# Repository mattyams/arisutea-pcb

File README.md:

# Arisutea - Arisu Keyboard PCB with More Modifications...now with MORE!

### Arisutea Keyboard Variants
- [STM32](https://github.com/mattyams/arisutea-pcb-stm32) - Prototypes Received. STM32F072 MCU, board is being tested.
- [SK6812MiniE](https://github.com/mattyams/arisutea-pcb-rgb) - In Progress. PCB designed, just need to do some QC.
- [Bluetooth](https://github.com/mattyams/arisutea-pcb-bt) - In Progress. Initial design for the PCB is ongoing, need to research more on the MCU and batteries.

## Disclaimer: Use these files at your own risk.
アリステア PCB designed using KiCad. The layout was originally created by FateNozomi, inspired by Lyn's EM7 and TGR Alice with some modification. The layout was then modified by CorruptedJef and robotictomato to add USB-C, ESD and to shift/add some keys. This inspired me to modify the layout further by adding the ability to swap your switches out whenever you want and to make some keys a little more permenant. I have designed many boards in the past but never a keyboard so this is my first crack at it and I figured why not go all out? If you notice any issue please open an issue and we can discuss!

Since the layout has been modified yet again I decided to give the project a new name, Arisutea, which translates to Alistair. Obviously keeping the theme running here. 

Check out the iBOM [here](https://htmlpreview.github.io/?https://raw.githubusercontent.com/mattyams/arisutea-pcb/master/hardware/BOM/arisutea-rev1.0-ibom.html)! This was generated with [InteractiveHtmlBom](https://github.com/openscopeproject/InteractiveHtmlBom)!

Key modifications to the PCB:
- Added in Kailh Hotswap sockets.
- Addition of full backspace position, connected to switch 59 (row 0, column 13).
  - Removed switch 63 and repositioned switch 59 to add full backspace position.
- USB-C ESD rework.
- Added underglow LED strip support (v0.6+)
- Added LED indicators for CAPS and NUM lock as well as layer. (v0.6+)
- Updated JSON layout file for this particular keyboard.
- Original mounting holes have been returned to their rightful place. The idea of widening them was good at the time for FR4 plates, but not very practical. I am redesigning the case to allow for brass inserts and standoffs to be installed so the PCB will be nice and snug. More on that later. FR4 plates still will work but you will have to drill the holes out manually. If you take this route....go forth cautiously adventurer.

Renders generated by [Tracespace](https://github.com/tracespace/tracespace).

v0.6+

Just some recent builds...

Messing around with different switches.

# QMK Firmware
This can be located in the [firmware](https://github.com/mattyams/arisutea-pcb/tree/master/firmware) folder. 

# Case Files for Ponoko

Case files are updated to reflect changes to the full backspace on switch 59 and can be found in the hardware folder under [arisutea-case](https://github.com/mattyams/arisutea-pcb/tree/master/hardware/arisutea-case).  The case I ordered with these changes just came in this week (3/6/2021) and it works very well with the changes I made to the full backspace and addition of the stablizer on the prototypes designed by CorruptedJef and robotictomato. There is now a "boxed" version of the case that I have made that is designed to work with some wrist rests that do not have the ortho shape AND case files for version 0.6+ PCBs that include the indicator LEDs, I have not ordered/tested these but will soon.

# FR4 Plates and Case

Additionaly I have created files for FR4 plates to be made and used with this layout. These can be found in the hardware folder under [FR4_Plates](https://github.com/mattyams/arisutea-pcb/tree/master/hardware/FR4_Plates). The plates are designed to fit with the full backspace and non-stepped capslock. That being said, these will not work on the original Fate Designs PCB. No plans to create plates for the LED indicators on the v0.6+ PCBs. NOTE FOR v0.6.3+ PCBs! FR4 plates still will work but you will have to drill the holes out manually. If you take this route....go forth cautiously adventurer.

## Exceprts from original designer, FateNozomi:

Key differences:
- Removed the extra [B] key on the right half and shifted the [NM,.?] row to the left by 0.25U.
- Shifted the 3 keys to the right and added arrow keys.
- Tweaked the bottom so that the 1.5U keys doesn't protrude out a little.

Shifting the [NM,.?] row to the left by 0.25U required quite some work on the arrangement of keys for the right half.
As a result, this does not give the same typing experience as Lyn's EM7 and TGR Alice.
Lyn's EM7 and TGR Alice uses the home row as the center point to vertically align both halves while I used the number row instead.
Due to the nature of staggered keyboards, aligning using the number row resulted in the home row not being aligned.

Disclaimer: Use these files at your own risk.

## Gerber Files
Download the gerber files under [releases](https://github.com/mattyams/arisutea-pcb/releases).

## PCB Assembly
For the components required, you may refer to the bill of materials included along with the release as reference or load up the design file in KiCad.
All the components can be soldered using a regular soldering iron, though soldering the USB-C receptacle might be the biggest hurdle. I have made an adjustment to the USB footprint to allow for a little more error when handsoldering. POS files have been removed due to the overwhelming amount of compatibility issues of placement and selection. The BOM will remain for part numbers from LCSC and board placement.

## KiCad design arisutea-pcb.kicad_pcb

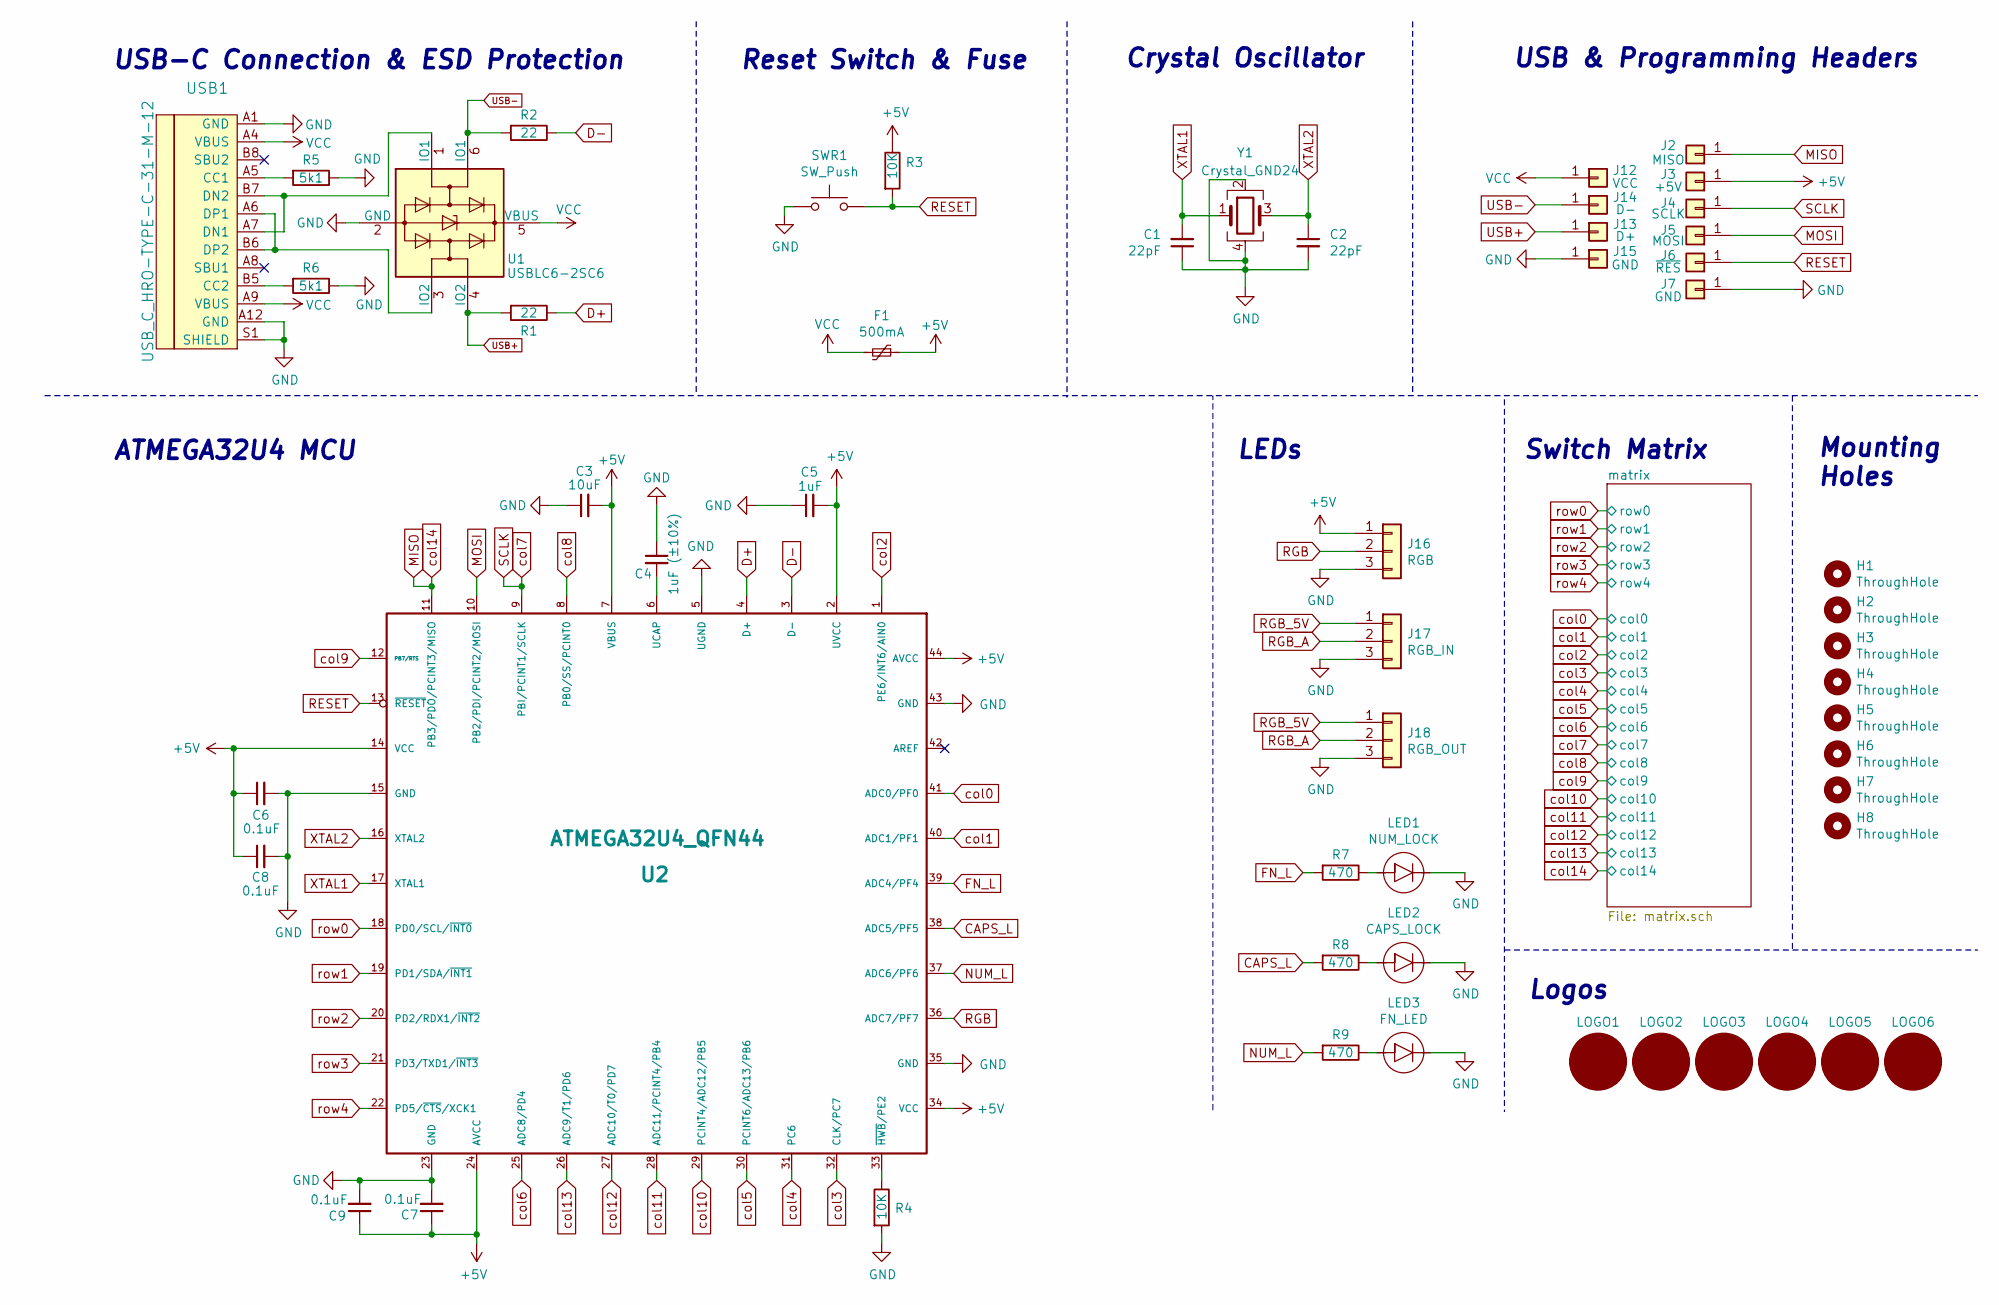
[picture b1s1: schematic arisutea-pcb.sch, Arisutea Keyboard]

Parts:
C1, C2: 22pF; C_0805_2012Metric_Pad1.18x1.45mm_HandSolder; LCSC C1804
C3: 10uF; C_0805_2012Metric_Pad1.18x1.45mm_HandSolder; LCSC C15850
C4: 1uF (±10%); C_0805_2012Metric_Pad1.18x1.45mm_HandSolder; LCSC C28323
C5: 1uF; C_0805_2012Metric_Pad1.18x1.45mm_HandSolder; LCSC C28323
C6, C7, C8, C9: 0.1uF; C_0805_2012Metric_Pad1.18x1.45mm_HandSolder; LCSC C28233
F1: 500mA; Fuse_1206_3216Metric_Pad1.42x1.75mm_HandSolder; LCSC C70068
H1, H2, H3, H4, H5, H6, H7, H8: ThroughHole; Generic-Mounthole
J2: MISO; PinHeader_1x01_P2.54mm_Vertical
J3: +5V; PinHeader_1x01_P2.54mm_Vertical
J4: SCLK; PinHeader_1x01_P2.54mm_Vertical
J5: MOSI; PinHeader_1x01_P2.54mm_Vertical
J6: ~RES~; PinHeader_1x01_P2.54mm_Vertical
J7, J15: GND; PinHeader_1x01_P2.54mm_Vertical
J12: VCC; PinHeader_1x01_P2.54mm_Vertical
J13: D+; PinHeader_1x01_P2.54mm_Vertical
J14: D-; PinHeader_1x01_P2.54mm_Vertical
J16: RGB; PinHeader_1x03_P2.54mm_Vertical
J17: RGB_IN; PinHeader_1x03_P2.54mm_Vertical
J18: RGB_OUT; PinHeader_1x03_P2.54mm_Vertical
LED1: NUM_LOCK; LED_IN-S124ARUW; LCSC C401114
LED2: CAPS_LOCK; LED_IN-S124ARUW; LCSC C401114
LED3: FN_LED; LED_IN-S124ARUW; LCSC C401114
LOGO1, LOGO2: arisutea_logo
LOGO3, LOGO4: QMK Logo; OSHW-Logo_11.4x12mm_SilkScreen
LOGO5, LOGO6: QMK_Logo_Light
R1, R2: 22; R_0805_2012Metric_Pad1.20x1.40mm_HandSolder; LCSC C17561
R3, R4: 10K; R_0805_2012Metric_Pad1.20x1.40mm_HandSolder; LCSC C17414
R5, R6: 5k1; R_0805_2012Metric_Pad1.20x1.40mm_HandSolder; LCSC C27834
R7, R8, R9: 470; R_0805_2012Metric_Pad1.20x1.40mm_HandSolder; LCSC C27834
SWR1: SW_Push; SW_SPST_TL3342; LCSC C318884
U1: USBLC6-2SC6; SOT-23-6_Handsoldering; LCSC C7519
U2: ATMEGA32U4_QFN44; TQFP-44_10x10mm_P0.8mm; LCSC C44854
USB1: USB_C_HRO-TYPE-C-31-M-12; USB_C_Receptacle_HRO_TYPE-C-31-M-12-HandSoldering; LCSC C319148
Y1: Crystal_GND24; Crystal_SMD_TXC_7M-4Pin_3.2x2.5mm_HandSoldering; LCSC C89371

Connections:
+5V: C3.2, C5.2, C6.1, C7.1, C8.1, C9.1, F1.1, J3.1, J16.1, R3.1, U2.2 (UVCC), U2.7 (VBUS), U2.14 (VCC), U2.24 (AVCC), U2.34 (VCC), U2.44 (AVCC)
CAPS_L: R8.2, U2.38 (ADC5/PF5)
D+: R1.1, U2.4 (D+)
D-: R2.1, U2.3 (D-)
FN_L: R7.2, U2.39 (ADC4/PF4)
GND: C1.1, C2.2, C3.1, C4.1, C5.1, C6.2, C7.2, C8.2, C9.2, J7.1, J15.1, J16.3, J17.3, J18.3, LED1.C, LED2.C, LED3.C, R4.2, R5.1, R6.1, SWR1.1, U1.2 (GND), U2.5 (UGND), U2.15 (GND), U2.23 (GND), U2.35 (GND), U2.43 (GND), USB1.A1 (GND), USB1.A12 (GND), USB1.S1 (SHIELD), Y1.2, Y1.4
MISO: J2.1, U2.11 (PB3/PDO/PCINT3/MISO); also elsewhere on the board
MOSI: J5.1, U2.10 (PB2/PDI/PCINT2/MOSI)
NUM_L: R9.2, U2.37 (ADC6/PF6)
unnamed: C4.2, U2.6 (UCAP)
unnamed: LED1.A, R7.1
unnamed: LED2.A, R8.1
unnamed: LED3.A, R9.1
unnamed: R4.1, U2.33 (~HWB~/PE2)
unnamed: R5.2, USB1.A5 (CC1)
unnamed: R6.2, USB1.B5 (CC2)
unnamed: U1.1 (IO1), USB1.A7 (DN1), USB1.B7 (DN2)
unnamed: U1.3 (IO2), USB1.A6 (DP1), USB1.B6 (DP2)
RESET: J6.1, R3.2, SWR1.2, U2.13 (~RESET~)
RGB: J16.2, U2.36 (ADC7/PF7)
RGB_5V: J17.1, J18.1
RGB_A: J17.2, J18.2
SCLK: J4.1, U2.9 (PBI/PCINT1/SCLK); also elsewhere on the board
USB+: J13.1, R1.2, U1.4 (IO2)
USB-: J14.1, R2.2, U1.6 (IO1)
VCC: F1.2, J12.1, U1.5 (VBUS), USB1.A4 (VBUS), USB1.A9 (VBUS)
XTAL1: C1.2, U2.17 (XTAL1), Y1.1
XTAL2: C2.1, U2.16 (XTAL2), Y1.3
col0: U2.41 (ADC0/PF0); also elsewhere on the board
col1: U2.40 (ADC1/PF1); also elsewhere on the board
col2: U2.1 (PE6/INT6/AIN0); also elsewhere on the board
col3: U2.32 (CLK/PC7); also elsewhere on the board
col4: U2.31 (PC6); also elsewhere on the board
col5: U2.30 (PCINT6/ADC13/PB6); also elsewhere on the board
col6: U2.25 (ADC8/PD4); also elsewhere on the board
col8: U2.8 (PB0/SS/PCINT0); also elsewhere on the board
col9: U2.12 (PB7/RTS); also elsewhere on the board
col10: U2.29 (PCINT4/ADC12/PB5); also elsewhere on the board
col11: U2.28 (ADC11/PCINT4/PB4); also elsewhere on the board
col12: U2.27 (ADC10/T0/PD7); also elsewhere on the board
col13: U2.26 (ADC9/T1/PD6); also elsewhere on the board
row0: U2.18 (PD0/SCL/~INT0~); also elsewhere on the board
row1: U2.19 (PD1/SDA/~INT1~); also elsewhere on the board
row2: U2.20 (PD2/RDX1/~INT2~); also elsewhere on the board
row3: U2.21 (PD3/TXD1/~INT3~); also elsewhere on the board
row4: U2.22 (PD5/~CTS~/XCK1); also elsewhere on the board

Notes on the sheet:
ATMEGA32U4 MCU
USB-C Connection & ESD Protection
Reset Switch & Fuse
Crystal Oscillator
USB & Programming Headers
LEDs
Switch Matrix
Logos
Mounting Holes

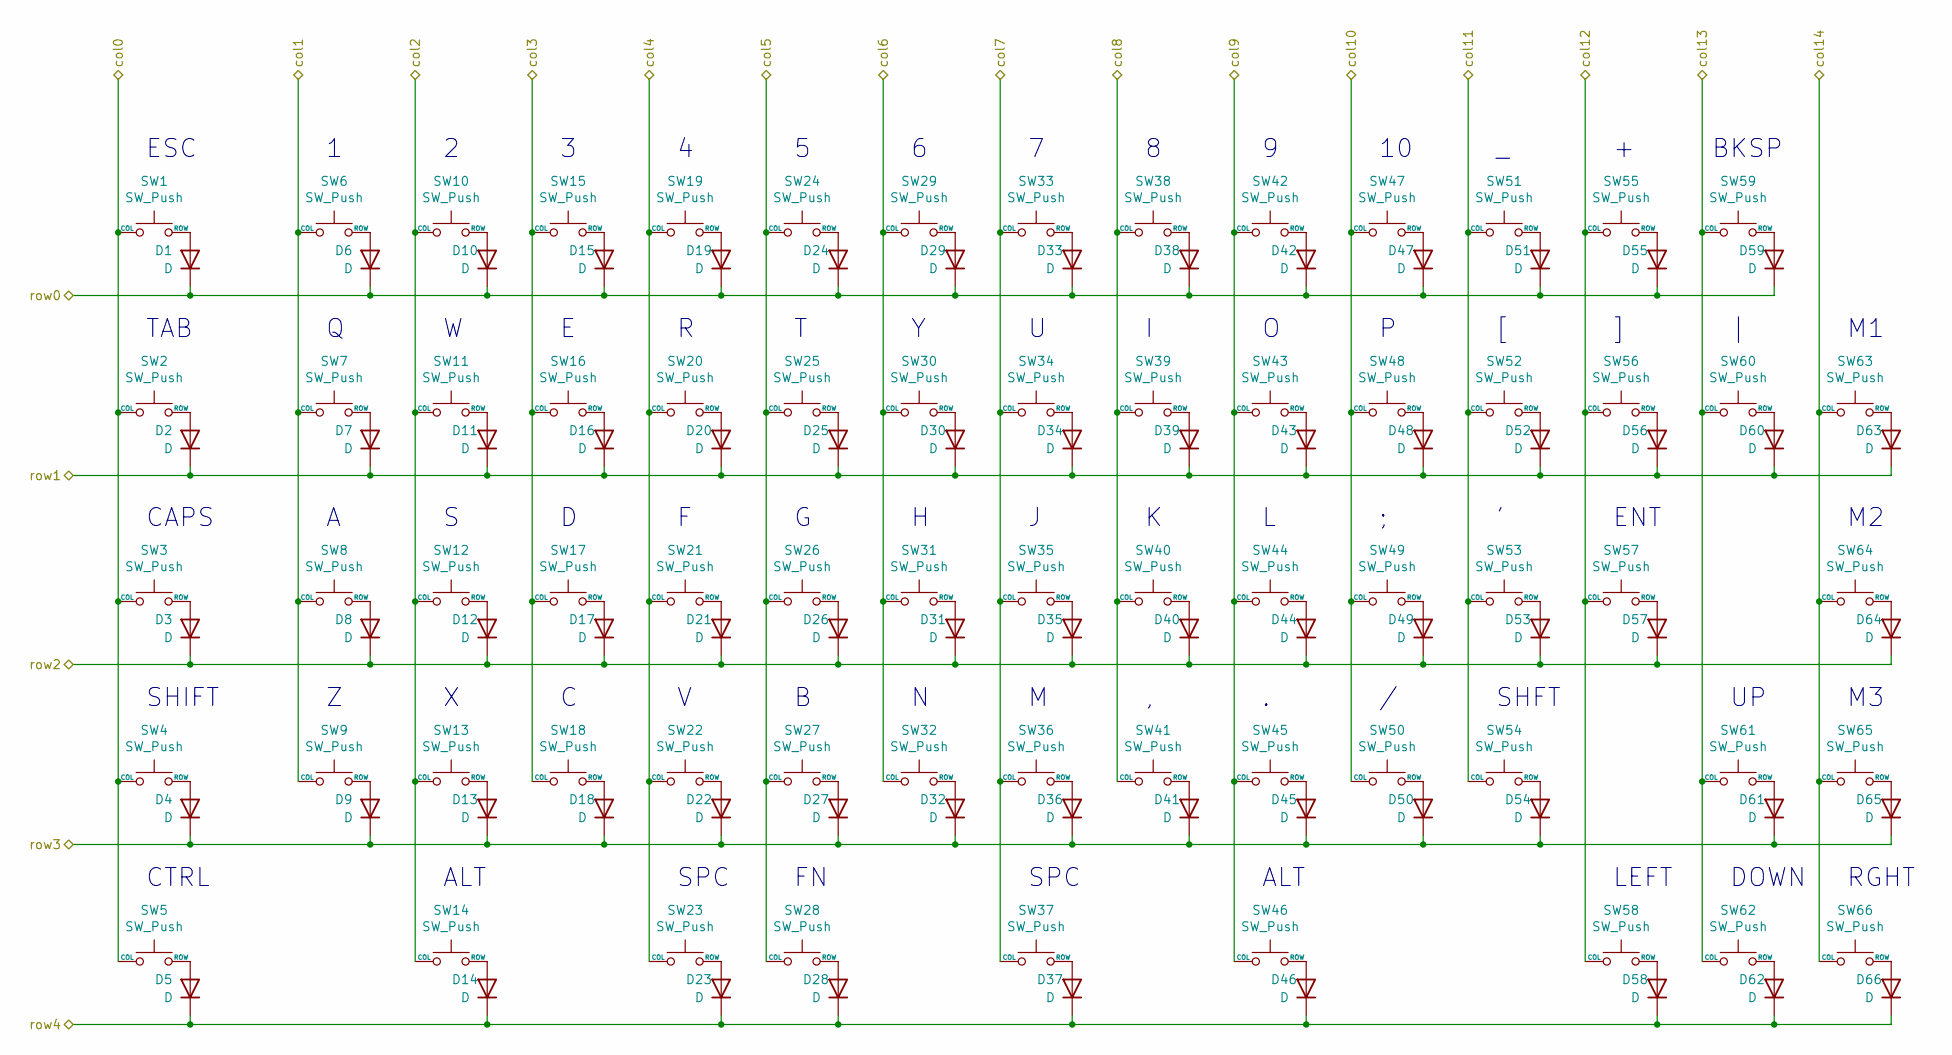
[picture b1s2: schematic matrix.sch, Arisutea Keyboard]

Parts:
D1, D2, D3, D4, D5, D6, D7, D8, D9, D10, D11, D12, D13, D14, D15, D16, D17, D18, D19, D20, D21, D22, D23, D24, D25, D26, D27, D28, D29, D30, D31, D32, D33, D34, D35, D36, D37, D38, D39, D40, D41, D42, D43, D44, D45, D46, D47, D48, D49, D50, D51, D52, D53, D54, D55, D56, D57, D58, D59, D60, D61, D62, D63, D64, D65, D66: D; D_SOD-123; LCSC C81598
SW1, SW6, SW7, SW8, SW9, SW10, SW11, SW12, SW13, SW14, SW15, SW16, SW17, SW18, SW19, SW20, SW21, SW22, SW24, SW25, SW26, SW27, SW28, SW29, SW30, SW31, SW32, SW33, SW34, SW35, SW36, SW38, SW39, SW40, SW41, SW42, SW43, SW44, SW45, SW46, SW47, SW48, SW49, SW50, SW51, SW52, SW53, SW55, SW56, SW58, SW61, SW62, SW63, SW64, SW65, SW66: SW_Push; SW_Hotswap_Kailh_1.00u
SW2, SW5, SW60: SW_Push; SW_Hotswap_Kailh_1.50u
SW3, SW54: SW_Push; SW_Hotswap_Kailh_1.75u
SW4: SW_Push; SW_Hotswap_Kailh_2.25u
SW23: SW_Push; SW_Hotswap_Kailh_2.00u_RevStab
SW37: SW_Push; SW_Hotswap_Kailh_2.75u_RevStab
SW57: SW_Push; SW_Hotswap_Kailh_2.25u_RevStab
SW59: SW_Push; SW_Hotswap_Kailh_2.00u

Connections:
MISO: SW63.1 (COL), SW64.1 (COL), SW65.1 (COL), SW66.1 (COL); also elsewhere on the board
unnamed: D1.2 (A), SW1.2 (ROW)
unnamed: D2.2 (A), SW2.2 (ROW)
unnamed: D3.2 (A), SW3.2 (ROW)
unnamed: D4.2 (A), SW4.2 (ROW)
unnamed: D5.2 (A), SW5.2 (ROW)
unnamed: D6.2 (A), SW6.2 (ROW)
unnamed: D7.2 (A), SW7.2 (ROW)
unnamed: D8.2 (A), SW8.2 (ROW)
unnamed: D9.2 (A), SW9.2 (ROW)
unnamed: D10.2 (A), SW10.2 (ROW)
unnamed: D11.2 (A), SW11.2 (ROW)
unnamed: D12.2 (A), SW12.2 (ROW)
unnamed: D13.2 (A), SW13.2 (ROW)
unnamed: D14.2 (A), SW14.2 (ROW)
unnamed: D15.2 (A), SW15.2 (ROW)
unnamed: D16.2 (A), SW16.2 (ROW)
unnamed: D17.2 (A), SW17.2 (ROW)
unnamed: D18.2 (A), SW18.2 (ROW)
unnamed: D19.2 (A), SW19.2 (ROW)
unnamed: D20.2 (A), SW20.2 (ROW)
unnamed: D21.2 (A), SW21.2 (ROW)
unnamed: D22.2 (A), SW22.2 (ROW)
unnamed: D23.2 (A), SW23.2 (ROW)
unnamed: D24.2 (A), SW24.2 (ROW)
unnamed: D25.2 (A), SW25.2 (ROW)
unnamed: D26.2 (A), SW26.2 (ROW)
unnamed: D27.2 (A), SW27.2 (ROW)
unnamed: D28.2 (A), SW28.2 (ROW)
unnamed: D29.2 (A), SW29.2 (ROW)
unnamed: D30.2 (A), SW30.2 (ROW)
unnamed: D31.2 (A), SW31.2 (ROW)
unnamed: D32.2 (A), SW32.2 (ROW)
unnamed: D33.2 (A), SW33.2 (ROW)
unnamed: D34.2 (A), SW34.2 (ROW)
unnamed: D35.2 (A), SW35.2 (ROW)
unnamed: D36.2 (A), SW36.2 (ROW)
unnamed: D37.2 (A), SW37.2 (ROW)
unnamed: D38.2 (A), SW38.2 (ROW)
unnamed: D39.2 (A), SW39.2 (ROW)
unnamed: D40.2 (A), SW40.2 (ROW)
unnamed: D41.2 (A), SW41.2 (ROW)
unnamed: D42.2 (A), SW42.2 (ROW)
unnamed: D43.2 (A), SW43.2 (ROW)
unnamed: D44.2 (A), SW44.2 (ROW)
unnamed: D45.2 (A), SW45.2 (ROW)
unnamed: D46.2 (A), SW46.2 (ROW)
unnamed: D47.2 (A), SW47.2 (ROW)
unnamed: D48.2 (A), SW48.2 (ROW)
unnamed: D49.2 (A), SW49.2 (ROW)
unnamed: D50.2 (A), SW50.2 (ROW)
unnamed: D51.2 (A), SW51.2 (ROW)
unnamed: D52.2 (A), SW52.2 (ROW)
unnamed: D53.2 (A), SW53.2 (ROW)
unnamed: D54.2 (A), SW54.2 (ROW)
unnamed: D55.2 (A), SW55.2 (ROW)
unnamed: D56.2 (A), SW56.2 (ROW)
unnamed: D57.2 (A), SW57.2 (ROW)
unnamed: D58.2 (A), SW58.2 (ROW)
unnamed: D59.2 (A), SW59.2 (ROW)
unnamed: D60.2 (A), SW60.2 (ROW)
unnamed: D61.2 (A), SW61.2 (ROW)
unnamed: D62.2 (A), SW62.2 (ROW)
unnamed: D63.2 (A), SW63.2 (ROW)
unnamed: D64.2 (A), SW64.2 (ROW)
unnamed: D65.2 (A), SW65.2 (ROW)
unnamed: D66.2 (A), SW66.2 (ROW)
SCLK: SW33.1 (COL), SW34.1 (COL), SW35.1 (COL), SW36.1 (COL), SW37.1 (COL); also elsewhere on the board
col0: SW1.1 (COL), SW2.1 (COL), SW3.1 (COL), SW4.1 (COL), SW5.1 (COL); also elsewhere on the board
col1: SW6.1 (COL), SW7.1 (COL), SW8.1 (COL), SW9.1 (COL); also elsewhere on the board
col2: SW10.1 (COL), SW11.1 (COL), SW12.1 (COL), SW13.1 (COL), SW14.1 (COL); also elsewhere on the board
col3: SW15.1 (COL), SW16.1 (COL), SW17.1 (COL), SW18.1 (COL); also elsewhere on the board
col4: SW19.1 (COL), SW20.1 (COL), SW21.1 (COL), SW22.1 (COL), SW23.1 (COL); also elsewhere on the board
col5: SW24.1 (COL), SW25.1 (COL), SW26.1 (COL), SW27.1 (COL), SW28.1 (COL); also elsewhere on the board
col6: SW29.1 (COL), SW30.1 (COL), SW31.1 (COL), SW32.1 (COL); also elsewhere on the board
col8: SW38.1 (COL), SW39.1 (COL), SW40.1 (COL), SW41.1 (COL); also elsewhere on the board
col9: SW42.1 (COL), SW43.1 (COL), SW44.1 (COL), SW45.1 (COL), SW46.1 (COL); also elsewhere on the board
col10: SW47.1 (COL), SW48.1 (COL), SW49.1 (COL), SW50.1 (COL); also elsewhere on the board
col11: SW51.1 (COL), SW52.1 (COL), SW53.1 (COL), SW54.1 (COL); also elsewhere on the board
col12: SW55.1 (COL), SW56.1 (COL), SW57.1 (COL), SW58.1 (COL); also elsewhere on the board
col13: SW59.1 (COL), SW60.1 (COL), SW61.1 (COL), SW62.1 (COL); also elsewhere on the board
row0: D1.1 (K), D6.1 (K), D10.1 (K), D15.1 (K), D19.1 (K), D24.1 (K), D29.1 (K), D33.1 (K), D38.1 (K), D42.1 (K), D47.1 (K), D51.1 (K), D55.1 (K), D59.1 (K); also elsewhere on the board
row1: D2.1 (K), D7.1 (K), D11.1 (K), D16.1 (K), D20.1 (K), D25.1 (K), D30.1 (K), D34.1 (K), D39.1 (K), D43.1 (K), D48.1 (K), D52.1 (K), D56.1 (K), D60.1 (K), D63.1 (K); also elsewhere on the board
row2: D3.1 (K), D8.1 (K), D12.1 (K), D17.1 (K), D21.1 (K), D26.1 (K), D31.1 (K), D35.1 (K), D40.1 (K), D44.1 (K), D49.1 (K), D53.1 (K), D57.1 (K), D64.1 (K); also elsewhere on the board
row3: D4.1 (K), D9.1 (K), D13.1 (K), D18.1 (K), D22.1 (K), D27.1 (K), D32.1 (K), D36.1 (K), D41.1 (K), D45.1 (K), D50.1 (K), D54.1 (K), D61.1 (K), D65.1 (K); also elsewhere on the board
row4: D5.1 (K), D14.1 (K), D23.1 (K), D28.1 (K), D37.1 (K), D46.1 (K), D58.1 (K), D62.1 (K), D66.1 (K); also elsewhere on the board

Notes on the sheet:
ESC
TAB
ENT
RGHT
LEFT
DOWN
SPC
ALT
CTRL
SHFT
SHIFT
CAPS
BKSP

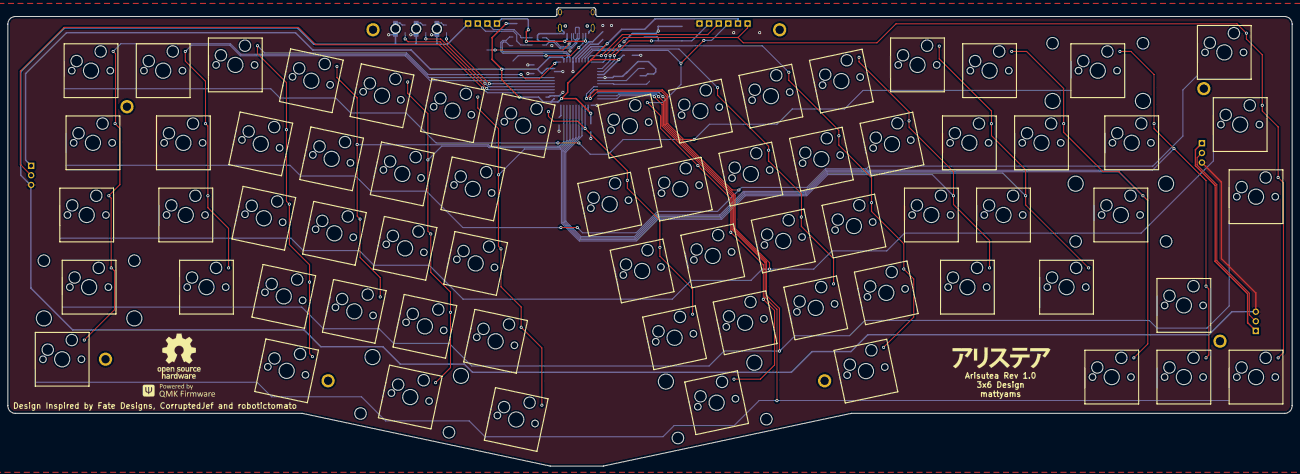
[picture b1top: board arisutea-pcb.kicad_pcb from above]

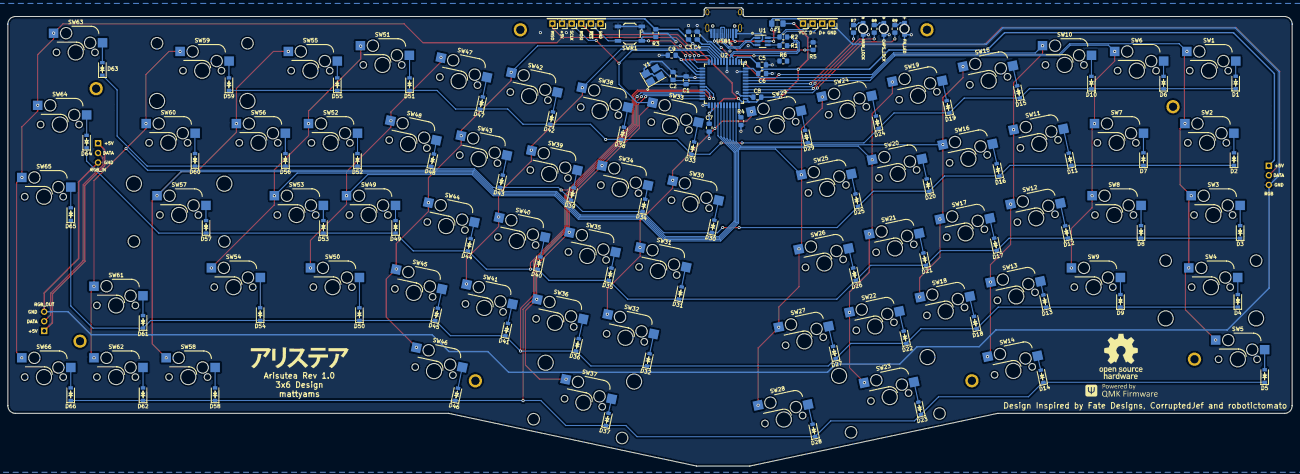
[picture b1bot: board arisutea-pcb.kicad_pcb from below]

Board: 2 copper layers, 339.1 x 121.0 mm, 186 parts (109 on the bottom side), 112 nets.

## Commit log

2021-05-04 v0.6.3
    - Updated mounting holes for new case design.
    - Removed matte case as the regular file can be used for either.
    - Library update.
    - Gerbies regenerated for version bump.
    - iBOM added.
    - README for most pages edited.
2021-05-04 update file name
2021-05-05 graphics update
2021-05-05 License update
2021-05-10 update firmware naming
2021-05-22 Version 1.0 Release
    Release of version 1.
    - Libraries have been merged for easier access.
    - Moved one cap a little closer to the MCU.
    - Regenerated gerbies, BOM and POS files.
    - New iBOM.
    - Bumped version number.
2021-05-25 case corrections
    Caught an error in the design of the lopro case that would duplicate the switch cutouts and cause the cost and/or cutting time to increase. Removed faulty lines and regenerated case files. :100:
2021-05-25 Add OSHW mark
2021-05-26 fixed USB net names
2021-05-27 fixed another case error
2021-05-28 remove dupe lines
2021-07-14 remove POS files for SMT assembly
    It was becoming apparent that there were too many placement issues with JLCPCB (and maybe other fab houses too) to warrant this file existing. I had made it as a courtesy but nearly everyone that has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
